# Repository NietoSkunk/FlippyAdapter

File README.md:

# FlippyAdapter

IDE Ribbon Cable Adapter for the [Luminator MAX3000](https://github.com/NietoSkunk/FlippyDriver) Flip Dot Panel.

This exists to solve an issue with the FlippyDriver, namely that the driver is physically attached to the board and extends outside the footprint of the panel. 

It supports both 34- and 40-pin IDE ribbon cables, or any form of 0.1" IDC connector.

## Cloning repository (with Submodules)

```bash
$ git clone --recurse-submodules git@github.com:NietoSkunk/FlippyAdapter.git
```

## Production notes

* When populating 34-pin IDC connector headers, the connectors should be in the center of the board, such that there are six pins on the outside edges of each connector. 
* The headers may be populated upside down to mechanically fit, although care should be taken to ensure the wiring does not get reversed at the other end of the ribbon cable.
* The two screw holes are M3 sized, and fit a 10mm M3 header to the holes in the board.

## Board Harness

| Pin | # | # | Pin |
| --- | - | - | --- |
| LED- | 1 | 2 | LED- |
| LED+ | 3 | 4 | LED+ |
| ROW_2_RESET | 5 | 6 | ROW_2_SET |
| ROW_4_RESET | 7 | 8 | ROW_4_SET |
| ROW_6_RESET | 9 | 10 | ROW_6_SET |
| ROW_8_RESET | 11 | 12 | ROW_8_SET |
| ROW_10_RESET | 13 | 14 | ROW_10_SET |
| ROW_12_RESET | 15 | 16 | ROW_12_SET |
| ROW_14_RESET | 17 | 18 | ROW_14_SET |
| ROW_16_RESET | 19 | 20 | ROW_16_SET |
| ROW_15_RESET | 21 | 22 | ROW_15_SET |
| ROW_13_RESET | 23 | 24 | ROW_13_SET |
| ROW_11_RESET | 25 | 26 | ROW_11_SET |
| ROW_9_RESET | 27 | 28 | ROW_9_SET |
| ROW_7_RESET | 29 | 30 | ROW_7_SET |
| ROW_5_RESET | 31 | 32 | ROW_5_SET |
| ROW_3_RESET | 33 | 34 | ROW_3_SET |
| ROW_1_RESET | 35 | 36 | ROW_1_SET |
| COL_2 | 37 | 38 | COL_1 |
| COL_4 | 39 | 40 | COL_3 |
| COL_6 | 41 | 42 | COL_5 |
| COL_8 | 43 | 44 | COL_7 |
| COL_10 | 45 | 46 | COL_9 |
| COL_12 | 47 | 48 | COL_11 |
| COL_14 | 49 | 50 | COL_13 |
| COL_16 | 51 | 52 | COL_15 |
| COL_18 | 53 | 54 | COL_17 |
| COL_20 | 55 | 56 | COL_19 |
| COL_22 | 57 | 58 | COL_21 |
| COL_24 | 59 | 60 | COL_23 |
| COL_26 | 61 | 62 | COL_25 |
| COL_28 | 63 | 64 | COL_27 |

## IDC Connectors

| Pin | # | # | Pin |
| --- | - | - | --- |
| N/C | 1 | 2 | N/C |
| N/C | 3 | 4 | N/C |
| N/C | 5 | 6 | N/C |
| LED- | 7 | 8 | LED- |
| LED- | 9 | 10 | LED- |
| LED+ | 11 | 12 | LED+ |
| LED+ | 13 | 14 | LED+ |
| ROW_2_RESET | 15 | 16 | ROW_2_SET |
| ROW_4_RESET | 17 | 18 | ROW_4_SET |
| ROW_6_RESET | 19 | 20 | ROW_6_SET |
| ROW_8_RESET | 21 | 22 | ROW_8_SET |
| ROW_10_RESET | 23 | 24 | ROW_10_SET |
| ROW_12_RESET | 25 | 26 | ROW_12_SET |
| ROW_14_RESET | 27 | 28 | ROW_14_SET |
| ROW_16_RESET | 29 | 30 | ROW_16_SET |
| ROW_15_RESET | 31 | 32 | ROW_15_SET |
| ROW_13_RESET | 33 | 34 | ROW_13_SET |
| ROW_11_RESET | 35 | 36 | ROW_11_SET |
| ROW_9_RESET | 37 | 38 | ROW_9_SET |
| ROW_7_RESET | 39 | 40 | ROW_7_SET |

| Pin | # | # | Pin |
| --- | - | - | --- |
| ROW_5_RESET | 1 | 2 | ROW_5_SET |
| ROW_3_RESET | 3 | 4 | ROW_3_SET |
| ROW_1_RESET | 5 | 6 | ROW_1_SET |
| COL_2 | 7 | 8 | COL_1 |
| COL_4 | 9 | 10 | COL_3 |
| COL_6 | 11 | 12 | COL_5 |
| COL_8 | 13 | 14 | COL_7 |
| COL_10 | 15 | 16 | COL_9 |
| COL_12 | 17 | 18 | COL_11 |
| COL_14 | 19 | 20 | COL_13 |
| COL_16 | 21 | 22 | COL_15 |
| COL_18 | 23 | 24 | COL_17 |
| COL_20 | 25 | 26 | COL_19 |
| COL_22 | 27 | 28 | COL_21 |
| COL_24 | 29 | 30 | COL_23 |
| COL_26 | 31 | 32 | COL_25 |
| COL_28 | 33 | 34 | COL_27 |
| N/C | 35 | 36 | N/C |
| N/C | 37 | 38 | N/C |
| N/C | 39 | 40 | N/C |

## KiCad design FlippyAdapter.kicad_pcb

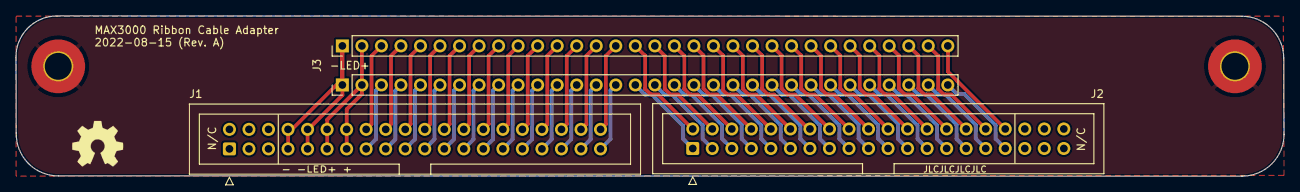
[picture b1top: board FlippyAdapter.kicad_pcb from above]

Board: 2 copper layers, 164.9 x 20.8 mm, 6 parts (0 on the bottom side), 63 nets.

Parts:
H1, H2: MountingHole_Pad; MountingHole_3.5mm_Pad_TopBottom
J1, J2: Conn_02x20_Odd_Even; IDC-Header_2x20_P2.54mm_Vertical
J3: Board Harness; Luminator_MAX3000
JLCJLCJLCJLC: JLCJLCJLCJLC; JLCPCB_OrderNumber

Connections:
+24V: J1.11, J1.12, J1.13, J1.14, J3.3, J3.4
COL_1: J2.8, J3.38
COL_2: J2.7, J3.37
COL_3: J2.10, J3.40
COL_4: J2.9, J3.39
COL_5: J2.12, J3.42
COL_6: J2.11, J3.41
COL_7: J2.14, J3.44
COL_8: J2.13, J3.43
COL_9: J2.16, J3.46
COL_10: J2.15, J3.45
COL_11: J2.18, J3.48
COL_12: J2.17, J3.47
COL_13: J2.20, J3.50
COL_14: J2.19, J3.49
COL_15: J2.22, J3.52
COL_16: J2.21, J3.51
COL_17: J2.24, J3.54
COL_18: J2.23, J3.53
COL_19: J2.26, J3.56
COL_20: J2.25, J3.55
COL_21: J2.28, J3.58
COL_22: J2.27, J3.57
COL_23: J2.30, J3.60
COL_24: J2.29, J3.59
COL_25: J2.32, J3.62
COL_26: J2.31, J3.61
COL_27: J2.34, J3.64
COL_28: J2.33, J3.63
PIN_GND: H1.1, H2.1
PIN_LED-: J1.7, J1.8, J1.9, J1.10, J3.1, J3.2
ROW_1_RESET: J2.5, J3.35
ROW_1_SET: J2.6, J3.36
ROW_2_RESET: J1.15, J3.5
ROW_2_SET: J1.16, J3.6
ROW_3_RESET: J2.3, J3.33
ROW_3_SET: J2.4, J3.34
ROW_4_RESET: J1.17, J3.7
ROW_4_SET: J1.18, J3.8
ROW_5_RESET: J2.1, J3.31
ROW_5_SET: J2.2, J3.32
ROW_6_RESET: J1.19, J3.9
ROW_6_SET: J1.20, J3.10
ROW_7_RESET: J1.39, J3.29
ROW_7_SET: J1.40, J3.30
ROW_8_RESET: J1.21, J3.11
ROW_8_SET: J1.22, J3.12
ROW_9_RESET: J1.37, J3.27
ROW_9_SET: J1.38, J3.28
ROW_10_RESET: J1.23, J3.13
ROW_10_SET: J1.24, J3.14
ROW_11_RESET: J1.35, J3.25
ROW_11_SET: J1.36, J3.26
ROW_12_RESET: J1.25, J3.15
ROW_12_SET: J1.26, J3.16
ROW_13_RESET: J1.33, J3.23
ROW_13_SET: J1.34, J3.24
ROW_14_RESET: J1.27, J3.17
ROW_14_SET: J1.28, J3.18
ROW_15_RESET: J1.31, J3.21
ROW_15_SET: J1.32, J3.22
ROW_16_RESET: J1.29, J3.19
ROW_16_SET: J1.30, J3.20

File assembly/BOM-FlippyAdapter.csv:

Comment,Designator,Footprint,LCSC
MountingHole_Pad,H1,MountingHole_3.5mm_Pad_TopBottom,
MountingHole_Pad,H2,MountingHole_3.5mm_Pad_TopBottom,
Board Harness,J3,Luminator_MAX3000,
Conn_02x20_Odd_Even,J1,IDC-Header_2x20_P2.54mm_Vertical,
Conn_02x20_Odd_Even,J2,IDC-Header_2x20_P2.54mm_Vertical,

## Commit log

2022-08-17 Initial Revision of Flippy Adapter
2022-08-25 Add libraries submodule
2022-08-25 Remove internal library
2022-08-25 Add pinouts to README
